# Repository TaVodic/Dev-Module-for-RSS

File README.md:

# Development Module for Safety Radar Sensor in Single-Track Vehicles

<!-- ### Features on PCB
* ESP32
    * BLE
    * MAC
    * 2 UARTs (flashing/debugging + radar interface)
    * $I^2C$ or SPI
* CP2102 USB-UART module
* PHY Ethernet module with connector
* IMU (6+3 DoF)
* Power management
* LED neopixel
* Buzzer
* Pogo pins – board to board connector
* ESP32 GPIO <-> radar pins (FFC conn)
* 100BASE-T1 connector
* ANT+ module -->

The RSS project includes two software repositories:

* ROS2 package as emulation of radar procesing unit and RSS demo module [(RSS_ROS2)](https://gitext.alps.cz/240703/rss_ros2)
* ESP-IDF project for ESP32 implementing uROS and all hardware peripherals [(RSS_uROS)](https://gitext.alps.cz/240703/rss_uros)

### [Schematic design](documents/RSS_schematic_v1.0.0.pdf)

### [Thesis](documents/Tavoda_semestral_thesis.pdf)

### [EEICT article](documents/Development_Module_for_Radar_Safety_Sensor_in_Single_Track_Vehicles.pdf)

### [Photo documentation](documents/visuals/)

### Block diagram

### Power management diagram

### ROS2 graph

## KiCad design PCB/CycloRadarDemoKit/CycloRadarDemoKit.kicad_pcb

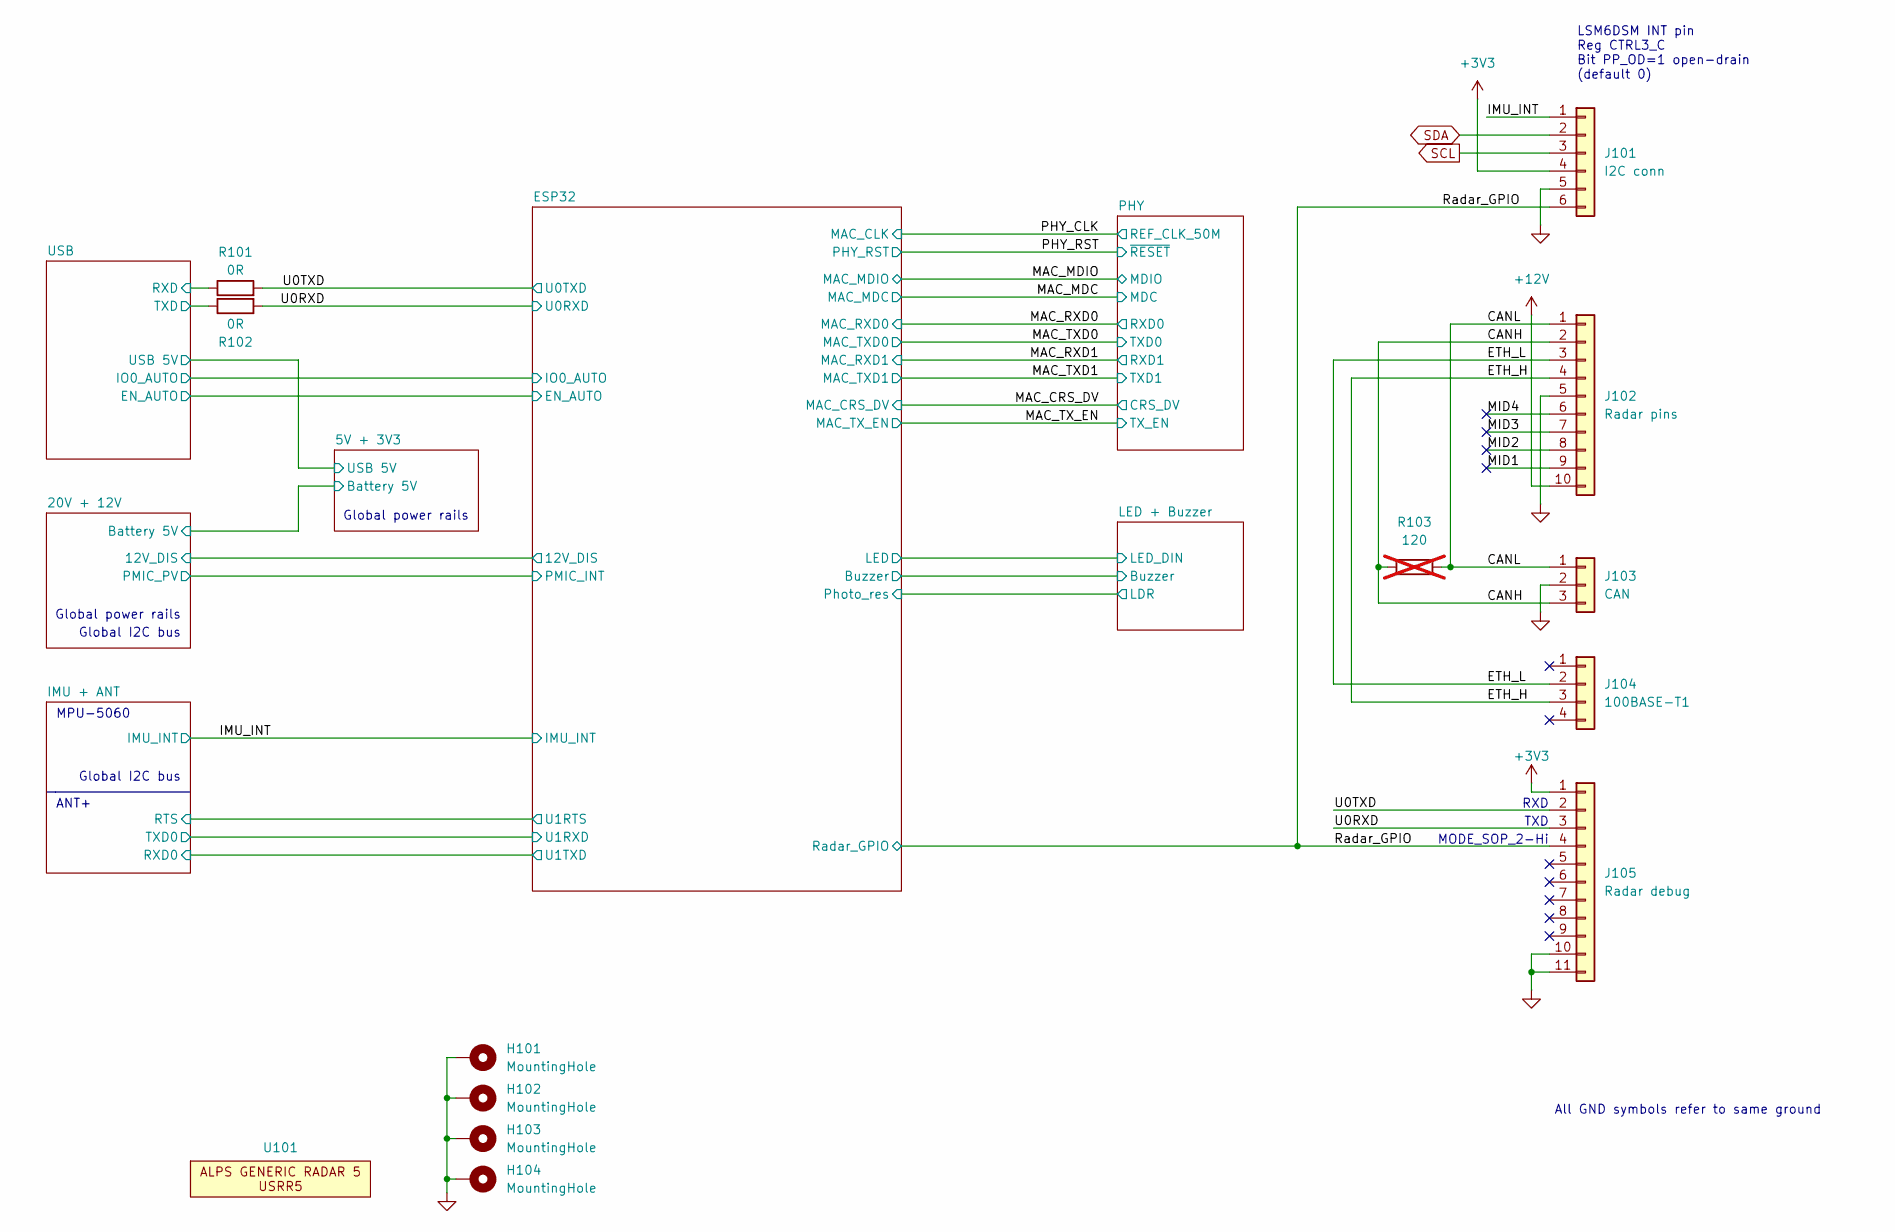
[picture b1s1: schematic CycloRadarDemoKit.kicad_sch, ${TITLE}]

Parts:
H101, H102, H103, H104: MountingHole; MountingHole_2.7mm_M2.5_ISO7380_Pad
J101: I2C conn; PinHeader_1x06_P1.27mm_Vertical
J102: Radar pins; PinHeader_1x10_P1.27mm_Vertical
J103: CAN; Molex_39501-1003; Mouser 538-39501-1003
J104: 100BASE-T1; Molex_347920040; Mouser 538-34792-0040
J105: Radar debug; AFC30-S10FCC-00; LCSC C395235
R101, R102: 0R; R_0805_2012Metric; LCSC C17477
R103: 120; R_0603_1608Metric; not fitted
U101: ALPS_USRR5_woPins

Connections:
+3V3: J101.4, J105.1; also elsewhere on the board
+12V: J102.10; also elsewhere on the board
/CANH: J102.2, J103.3, R103.1
/CANL: J102.1, J103.1, R103.2
/ETH_H: J102.4, J104.3
/ETH_L: J102.3, J104.2
/IMU_INT: J101.1; also elsewhere on the board
/MID1: J102.9
/MID2: J102.8
/MID3: J102.7
/MID4: J102.6
/Radar_GPIO: J101.6, J105.4; also elsewhere on the board
/U0RXD: J105.3, R102.2; also elsewhere on the board
/U0TXD: J105.2, R101.2; also elsewhere on the board
/USB/RXD: R101.1; also elsewhere on the board
/USB/TXD: R102.1; also elsewhere on the board
GND: H101.1, H102.1, H103.1, H104.1, J101.5, J102.5, J103.2, J105.10, J105.11; also elsewhere on the board
SCL: J101.3; also elsewhere on the board
SDA: J101.2; also elsewhere on the board

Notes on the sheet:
RXD
MPU-5060
ANT+
Global I2C bus
LSM6DSM INT pin Reg CTRL3_C Bit PP_OD=1 open-drain (default 0)
Global power rails
TXD
MODE_SOP_2-Hi
All GND symbols refer to same ground

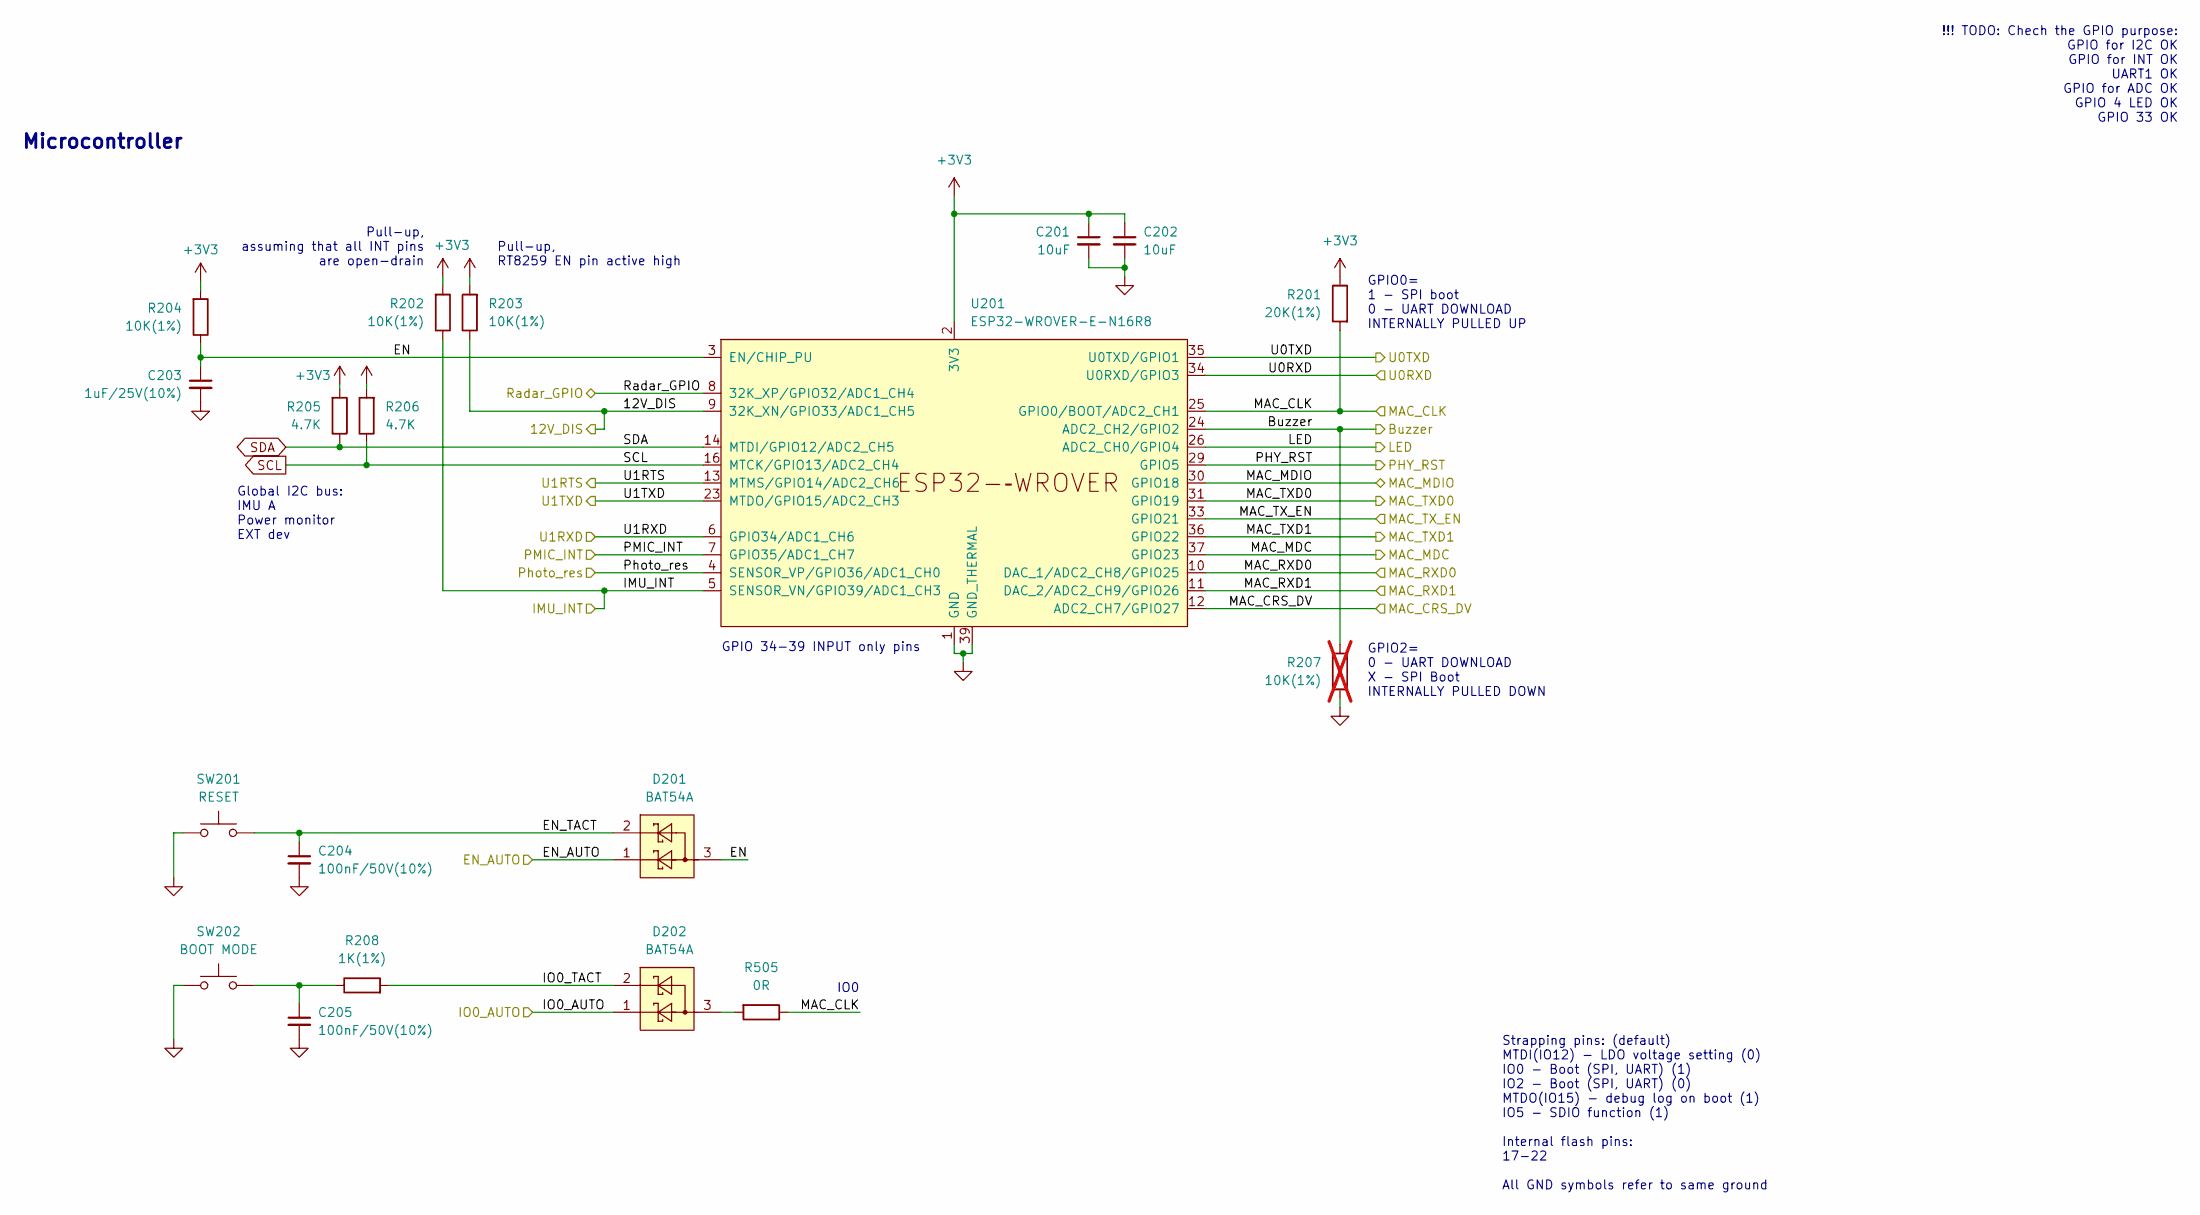
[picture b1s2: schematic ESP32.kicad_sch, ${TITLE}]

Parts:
C201, C202: 10uF; C_0603_1608Metric; LCSC C19702
C203: 1uF/25V(10%); C_0402_1005Metric; LCSC C52923
C204, C205: 100nF/50V(10%); C_0603_1608Metric; LCSC C14663
D201, D202: BAT54A; SOT-23; LCSC C283256
R201: 20K(1%); R_0603_1608Metric; LCSC C4184
R202, R203, R204: 10K(1%); R_0603_1608Metric; LCSC C25804
R205, R206: 4.7K; R_0603_1608Metric; LCSC C23162
R207: 10K(1%); R_0603_1608Metric; not fitted
R208: 1K(1%); R_0603_1608Metric; LCSC C21190
R505: 0R; R_0805_2012Metric; LCSC C17477
SW201: RESET; SW_SPST_TS-1088R; LCSC C455280
SW202: BOOT MODE; SW_SPST_TS-1088R; LCSC C455280
U201: ESP32-WROVER-E-N16R8; ESP32-WROVER-E_ThermalVias; LCSC C529589

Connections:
+3V3: C201.1, C202.1, R201.1, R202.2, R203.2, R204.2, R205.2, R206.2, U201.2 (3V3); also elsewhere on the board
/ESP32/12V_DIS: R203.1, U201.9 (32K_XN/GPIO33/ADC1_CH5); also elsewhere on the board
/ESP32/Buzzer: R207.1, U201.24 (ADC2_CH2/GPIO2); also elsewhere on the board
/ESP32/EN: C203.1, D201.3, R204.1, U201.3 (EN/CHIP_PU)
/ESP32/EN_AUTO: D201.1; also elsewhere on the board
/ESP32/EN_TACT: C204.1, D201.2, SW201.2
/ESP32/IO0_AUTO: D202.1; also elsewhere on the board
/ESP32/IO0_TACT: D202.2, R208.2
/ESP32/LED: U201.26 (ADC2_CH0/GPIO4); also elsewhere on the board
/ESP32/PMIC_INT: U201.7 (GPIO35/ADC1_CH7); also elsewhere on the board
/ESP32/Photo_res: U201.4 (SENSOR_VP/GPIO36/ADC1_CH0); also elsewhere on the board
/ESP32/U1RTS: U201.13 (MTMS/GPIO14/ADC2_CH6); also elsewhere on the board
/ESP32/U1RXD: U201.6 (GPIO34/ADC1_CH6); also elsewhere on the board
/ESP32/U1TXD: U201.23 (MTDO/GPIO15/ADC2_CH3); also elsewhere on the board
/IMU_INT: R202.1, U201.5 (SENSOR_VN/GPIO39/ADC1_CH3); also elsewhere on the board
/MAC_CRS_DV: U201.12 (ADC2_CH7/GPIO27); also elsewhere on the board
/MAC_MDC: U201.37 (GPIO23); also elsewhere on the board
/MAC_MDIO: U201.30 (GPIO18); also elsewhere on the board
/MAC_RXD0: U201.10 (DAC_1/ADC2_CH8/GPIO25); also elsewhere on the board
/MAC_RXD1: U201.11 (DAC_2/ADC2_CH9/GPIO26); also elsewhere on the board
/MAC_TXD0: U201.31 (GPIO19); also elsewhere on the board
/MAC_TXD1: U201.36 (GPIO22); also elsewhere on the board
/MAC_TX_EN: U201.33 (GPIO21); also elsewhere on the board
/PHY_CLK: R201.2, R505.1, U201.25 (GPIO0/BOOT/ADC2_CH1); also elsewhere on the board
/PHY_RST: U201.29 (GPIO5); also elsewhere on the board
/Radar_GPIO: U201.8 (32K_XP/GPIO32/ADC1_CH4); also elsewhere on the board
/U0RXD: U201.34 (U0RXD/GPIO3); also elsewhere on the board
/U0TXD: U201.35 (U0TXD/GPIO1); also elsewhere on the board
GND: C201.2, C202.2, C203.2, C204.2, C205.2, R207.2, SW201.1, SW202.1, U201.1 (GND), U201.15 (GND), U201.38 (GND), U201.39 (GND_THERMAL); also elsewhere on the board
unnamed: C205.1, R208.1, SW202.2
unnamed: D202.3, R505.2
SCL: R206.1, U201.16 (MTCK/GPIO13/ADC2_CH4); also elsewhere on the board
SDA: R205.1, U201.14 (MTDI/GPIO12/ADC2_CH5); also elsewhere on the board

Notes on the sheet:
GPIO2= 0 - UART DOWNLOAD X - SPI Boot INTERNALLY PULLED DOWN
Microcontroller
!!! TODO: Chech the GPIO purpose: GPIO for I2C OK GPIO for INT OK UART1 OK GPIO for ADC OK GPIO 4 LED OK GPIO 33 OK
Pull-up, RT8259 EN pin active high
GPIO0= 1 - SPI boot 0 - UART DOWNLOAD INTERNALLY PULLED UP
GPIO 34-39 INPUT only pins
Global I2C bus: IMU A Power monitor EXT dev
IO0
Strapping pins: (default) MTDI(IO12) - LDO voltage setting (0) IO0 - Boot (SPI, UART) (1) IO2 - Boot (SPI, UART) (0) MTDO(IO15) - debug log on boot (1) IO5 - SDIO function (1) Internal flash pins: 17-22 All GND symbols refer to same ground
Pull-up, assuming that all INT pins are open-drain

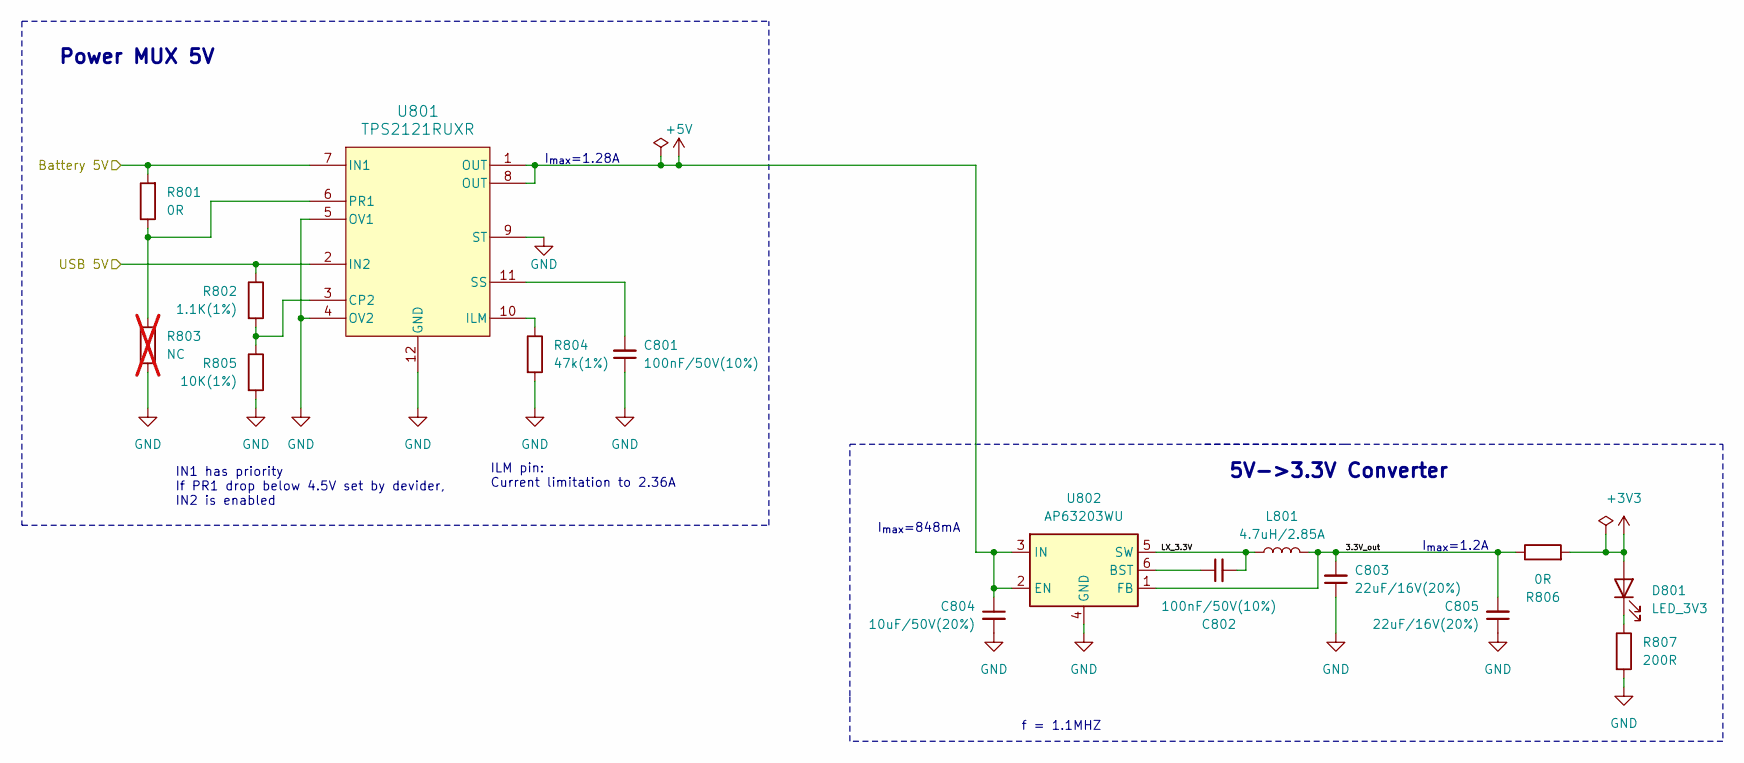
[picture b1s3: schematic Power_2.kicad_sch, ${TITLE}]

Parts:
C801, C802: 100nF/50V(10%); C_0603_1608Metric; LCSC C14663
C803, C805: 22uF/16V(20%); C_1206_3216Metric; LCSC C12891
C804: 10uF/50V(20%); C_1206_3216Metric; LCSC C13585
D801: LED_3V3; LED_0603_1608Metric; LCSC C497937
L801: 4.7uH/2.85A; L_Sunlord_SWPA4020S; LCSC C98363
R801, R806: 0R; R_0805_2012Metric; LCSC C17477
R802: 1.1K(1%); R_0603_1608Metric; LCSC C22764
R803: NC; R_0805_2012Metric; not fitted
R804: 47k(1%); R_0603_1608Metric; LCSC C25819
R805: 10K(1%); R_0603_1608Metric; LCSC C25804
R807: 200R; R_0603_1608Metric; LCSC C8218
U801: TPS2121RUXR; TPS2121; LCSC C485916
U802: AP63203WU; TSOT-23-6; LCSC C780769

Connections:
+3V3: D801.2 (A), R806.2; also elsewhere on the board
+5V: C804.1, U801.1 (OUT), U801.8 (OUT), U802.2 (EN), U802.3 (IN); also elsewhere on the board
/5V + 3V3/3.3V_out: C803.2, C805.2, L801.2, R806.1, U802.1 (FB)
/5V + 3V3/LX_3.3V: C802.2, L801.1, U802.5 (SW)
/5V + 3V3/USB 5V: R802.1, U801.2 (IN2); also elsewhere on the board
/20V + 12V/Battery 5V: R801.2, U801.7 (IN1); also elsewhere on the board
GND: C801.1, C803.1, C804.2, C805.1, R803.1, R804.2, R805.2, R807.2, U801.4 (OV2), U801.5 (OV1), U801.9 (ST), U801.12 (GND), U802.4 (GND); also elsewhere on the board
unnamed: D801.1 (K), R807.1
unnamed: R802.2, R805.1, U801.3 (CP2)
unnamed: R804.1, U801.10 (ILM)
unnamed: R801.1, R803.2, U801.6 (PR1)
unnamed: C801.2, U801.11 (SS)
unnamed: C802.1, U802.6 (BST)

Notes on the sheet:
ILM pin: Current limitation to 2.36A
IN1 has priority If PR1 drop below 4.5V set by devider, IN2 is enabled
I_{max}=1.2A
I_{max}=848mA
5V->3.3V Converter
I_{max}=1.28A
Power MUX 5V
f = 1.1MHZ

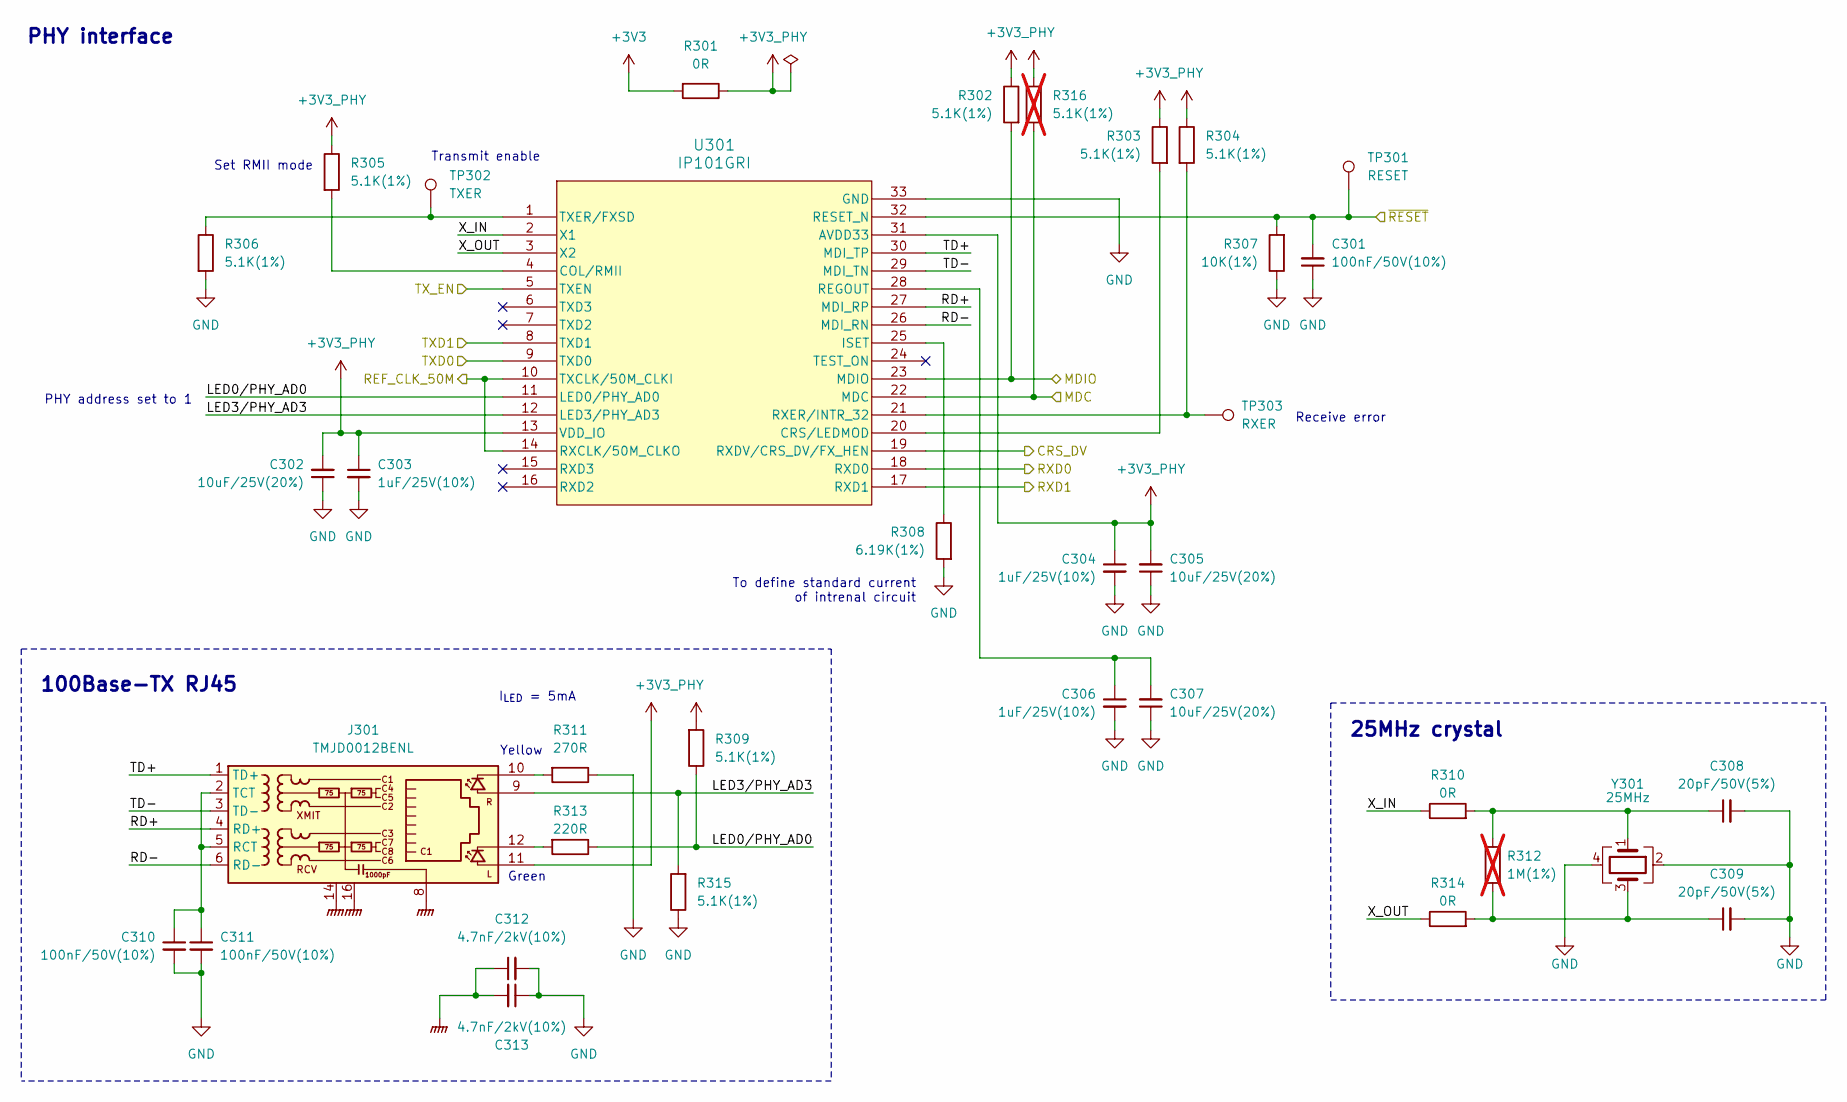
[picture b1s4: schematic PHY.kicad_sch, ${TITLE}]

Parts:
C301, C310, C311: 100nF/50V(10%); C_0603_1608Metric; LCSC C14663
C302: 10uF/25V(20%); C_0402_1005Metric; LCSC C15525
C303, C304, C306: 1uF/25V(10%); C_0402_1005Metric; LCSC C52923
C305, C307: 10uF/25V(20%); C_0603_1608Metric; LCSC C96446
C308, C309: 20pF/50V(5%); C_0402_1005Metric; LCSC C182483
C312, C313: 4.7nF/2kV(10%); C_1206_3216Metric; LCSC C41017
J301: TMJD0012BENL; RJ45_Taoglas_TMJD0012BENL; Mouser 960-TMJD0012BENL
R301: 0R; R_0805_2012Metric; LCSC C17477
R302, R303, R304, R305, R306, R309, R315: 5.1K(1%); R_0603_1608Metric; LCSC C23186
R307: 10K(1%); R_0603_1608Metric; LCSC C25804
R308: 6.19K(1%); R_0603_1608Metric; LCSC C403300
R310, R314: 0R; R_0603_1608Metric; LCSC C21189
R311: 270R; R_0603_1608Metric; LCSC C22966
R312: 1M(1%); R_0603_1608Metric; not fitted
R313: 220R; R_0603_1608Metric; LCSC C22962
R316: 5.1K(1%); R_0603_1608Metric; not fitted
TP301: RESET; TestPoint_Pad_D1.0mm
TP302: TXER; TestPoint_Pad_D1.0mm
TP303: RXER; TestPoint_Pad_D1.0mm
U301: IP101GRI; QFN_IP101GRI_WIZ; LCSC C703537
Y301: 25MHz; Crystal_SMD_3225-4Pin_3.2x2.5mm; LCSC C3003239

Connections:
+3V3: R301.2; also elsewhere on the board
+3V3_PHY: C302.2, C303.1, C304.1, C305.2, J301.11, R301.1, R302.1, R303.1, R304.1, R305.1, R309.2, R316.1, U301.13 (VDD_IO), U301.31 (AVDD33)
/MAC_CRS_DV: U301.19 (RXDV/CRS_DV/FX_HEN); also elsewhere on the board
/MAC_MDC: R316.2, U301.22 (MDC); also elsewhere on the board
/MAC_MDIO: R302.2, U301.23 (MDIO); also elsewhere on the board
/MAC_RXD0: U301.18 (RXD0); also elsewhere on the board
/MAC_RXD1: U301.17 (RXD1); also elsewhere on the board
/MAC_TXD0: U301.9 (TXD0); also elsewhere on the board
/MAC_TXD1: U301.8 (TXD1); also elsewhere on the board
/MAC_TX_EN: U301.5 (TXEN); also elsewhere on the board
/PHY/LED0/PHY_AD0: R309.1, R313.1, U301.11 (LED0/PHY_AD0)
/PHY/LED3/PHY_AD3: J301.9, R315.2, U301.12 (LED3/PHY_AD3)
/PHY/RD+: J301.4 (RD+), U301.27 (MDI_RP)
/PHY/RD-: J301.6 (RD-), U301.26 (MDI_RN)
/PHY/TD+: J301.1 (TD+), U301.30 (MDI_TP)
/PHY/TD-: J301.3 (TD-), U301.29 (MDI_TN)
/PHY/X_IN: R310.1, U301.2 (X1)
/PHY/X_OUT: R314.1, U301.3 (X2)
/PHY_CLK: U301.10 (TXCLK/50M_CLKI), U301.14 (RXCLK/50M_CLKO); also elsewhere on the board
/PHY_RST: C301.2, R307.2, TP301.1, U301.32 (RESET_N); also elsewhere on the board
GND: C301.1, C302.1, C303.2, C304.2, C305.1, C306.2, C307.1, C308.2, C309.2, C310.2, C311.2, C312.2, C313.1, R306.2, R307.1, R308.2, R311.1, R315.1, U301.33 (GND), Y301.2, Y301.4; also elsewhere on the board
GNDPWR: C312.1, C313.2, J301.8, J301.14, J301.16
unnamed: C308.1, R310.2, R312.2, Y301.1
unnamed: C309.1, R312.1, R314.2, Y301.3
unnamed: J301.10, R311.2
unnamed: J301.12, R313.2
unnamed: C310.1, C311.1, J301.2 (TCT), J301.5 (RCT)
unnamed: R305.2, U301.4 (COL/RMII)
unnamed: R303.2, U301.20 (CRS/LEDMOD)
unnamed: R308.1, U301.25 (ISET)
unnamed: C306.1, C307.2, U301.28 (REGOUT)
unnamed: R304.2, TP303.1, U301.21 (RXER/INTR_32)
unnamed: R306.1, TP302.1, U301.1 (TXER/FXSD)

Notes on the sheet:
Green
100Base-TX RJ45
I_{LED} = 5mA
25MHz crystal
PHY interface
Receive error
Set RMII mode
Yellow
Transmit enable
PHY address set to 1
To define standard current of intrenal circuit

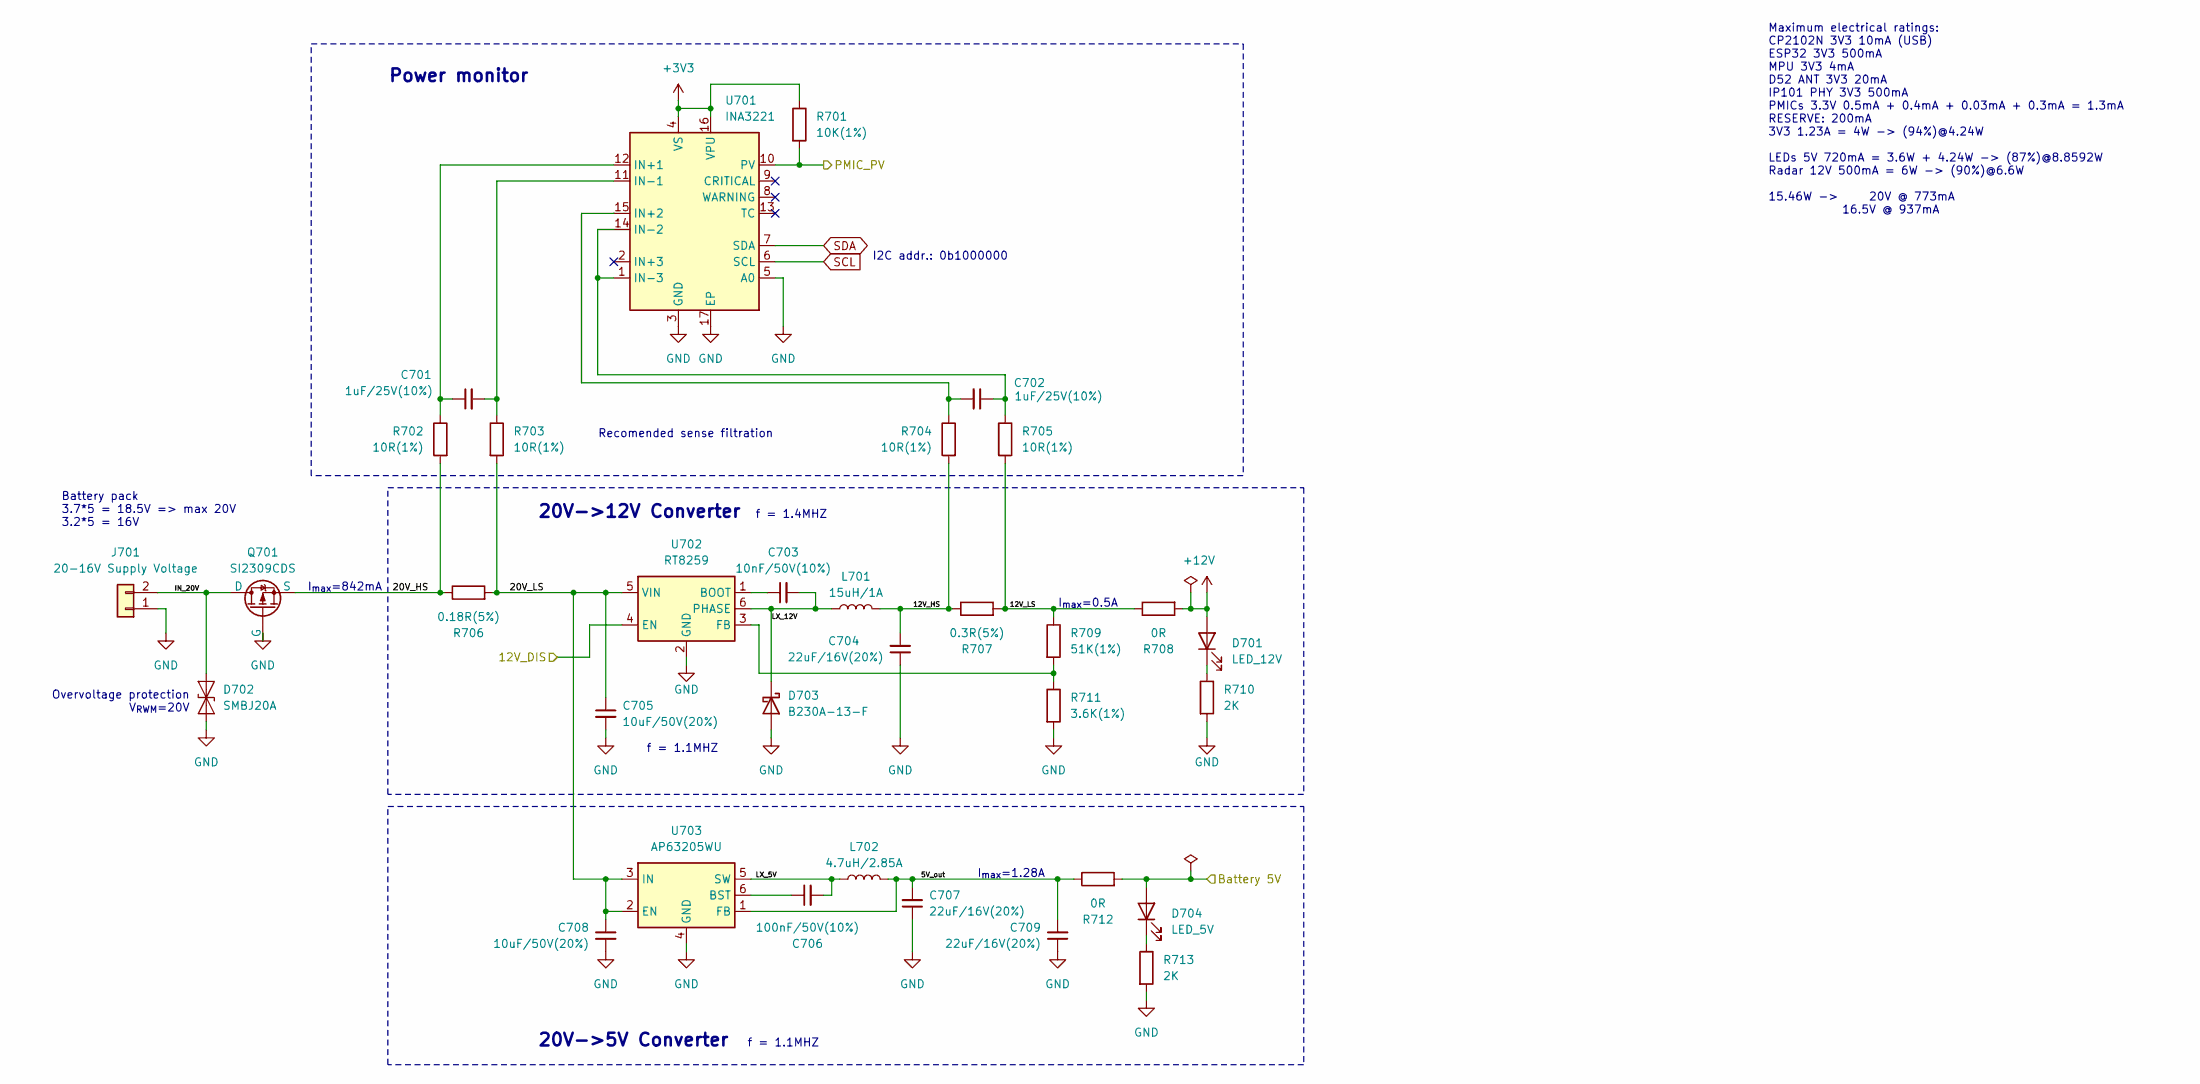
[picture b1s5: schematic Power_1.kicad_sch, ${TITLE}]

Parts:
C701, C702: 1uF/25V(10%); C_0402_1005Metric; LCSC C52923
C703: 10nF/50V(10%); C_0603_1608Metric; LCSC C57112
C704, C707, C709: 22uF/16V(20%); C_1206_3216Metric; LCSC C12891
C705, C708: 10uF/50V(20%); C_1206_3216Metric; LCSC C13585
C706: 100nF/50V(10%); C_0603_1608Metric; LCSC C14663
D701: LED_12V; LED_0603_1608Metric; LCSC C284922
D702: SMBJ20A; D_SMB; LCSC C3001979
D703: B230A-13-F; D_SMA; LCSC C12889
D704: LED_5V; LED_0603_1608Metric; LCSC C87326
J701: 20-16V Supply Voltage; Molex_39521-1002; Mouser 538-39521-1002
L701: 15uH/1A; L_Changjiang_FNR4018S; LCSC C167809
L702: 4.7uH/2.85A; L_Sunlord_SWPA4020S; LCSC C98363
Q701: SI2309CDS; SOT-23; LCSC C3021112
R701: 10K(1%); R_0603_1608Metric; LCSC C25804
R702, R703, R704, R705: 10R(1%); C_0603_1608Metric; LCSC C22859
R706: 0.18R(5%); R_Shunt_LTR10EVHJLR18; LCSC C253348
R707: 0.3R(5%); R_1210_3225Metric; LCSC C188102
R708, R712: 0R; R_0805_2012Metric; LCSC C17477
R709: 51K(1%); R_0603_1608Metric; LCSC C23196
R710, R713: 2K; R_0603_1608Metric; LCSC C22975
R711: 3.6K(1%); R_0603_1608Metric; LCSC C22980
U701: INA3221; Texas_RGV_S-PVQFN-N16_EP2.1x2.1mm; LCSC C181255
U702: RT8259; TSOT-23-6; LCSC C425775
U703: AP63205WU; TSOT-23-6; LCSC C2071056

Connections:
+3V3: R701.1, U701.4 (VS), U701.16 (VPU); also elsewhere on the board
+12V: D701.2 (A), R708.2; also elsewhere on the board
/20V + 12V/5V_out: C707.2, C709.2, L702.2, R712.1, U703.1 (FB)
/20V + 12V/12V_HS: C704.2, L701.2, R704.2, R707.1
/20V + 12V/12V_LS: R705.2, R707.2, R708.1, R709.1
/20V + 12V/20V_HS: Q701.3 (S), R702.2, R706.1
/20V + 12V/20V_LS: C705.1, C708.1, R703.2, R706.2, U702.5 (VIN), U703.2 (EN), U703.3 (IN)
/20V + 12V/Battery 5V: D704.2 (A), R712.2; also elsewhere on the board
/20V + 12V/IN_20V: D702.2 (A2), J701.2, Q701.1 (D)
/20V + 12V/LX_5V: C706.2, L702.1, U703.5 (SW)
/20V + 12V/LX_12V: C703.2, D703.1 (K), L701.1, U702.6 (PHASE)
/ESP32/12V_DIS: U702.4 (EN); also elsewhere on the board
/ESP32/PMIC_INT: R701.2, U701.10 (PV); also elsewhere on the board
GND: C704.1, C705.2, C707.1, C708.2, C709.1, D702.1 (A1), D703.2 (A), J701.1, Q701.2 (G), R710.2, R711.2, R713.2, U701.3 (GND), U701.5 (A0), U701.17 (EP), U702.2 (GND), U703.4 (GND); also elsewhere on the board
unnamed: D701.1 (K), R710.1
unnamed: D704.1 (K), R713.1
unnamed: C701.1, R702.1, U701.12 (IN+1)
unnamed: C702.2, R704.1, U701.15 (IN+2)
unnamed: C701.2, R703.1, U701.11 (IN-1)
unnamed: C702.1, R705.1, U701.1 (IN-3), U701.14 (IN-2)
unnamed: C703.1, U702.1 (BOOT)
unnamed: R709.2, R711.1, U702.3 (FB)
unnamed: C706.1, U703.6 (BST)
SCL: U701.6 (SCL); also elsewhere on the board
SDA: U701.7 (SDA); also elsewhere on the board

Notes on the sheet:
20V->5V Converter
20V->12V Converter
Overvoltage protection V_{RWM}=20V
f = 1.4MHZ
Maximum electrical ratings: CP2102N 3V3 10mA (USB) ESP32 3V3 500mA MPU 3V3 4mA D52 ANT 3V3 20mA IP101 PHY 3V3 500mA PMICs 3.3V 0.5mA + 0.4mA + 0.03mA + 0.3mA = 1.3mA RESERVE: 200mA 3V3 1.23A = 4W -> (94%)@4.24W LEDs 5V 720mA = 3.6W + 4.24W -> (87%)@8.8592W Radar 12V 500mA = 6W -> (90%)@6.6W 15.46W 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
I_{max}=842mA
I2C addr.: 0b1000000
Battery pack 3.7*5 = 18.5V => max 20V 3.2*5 = 16V
I_{max}=1.28A
Power monitor
f = 1.1MHZ
Recomended sense filtration
I_{max}=0.5A

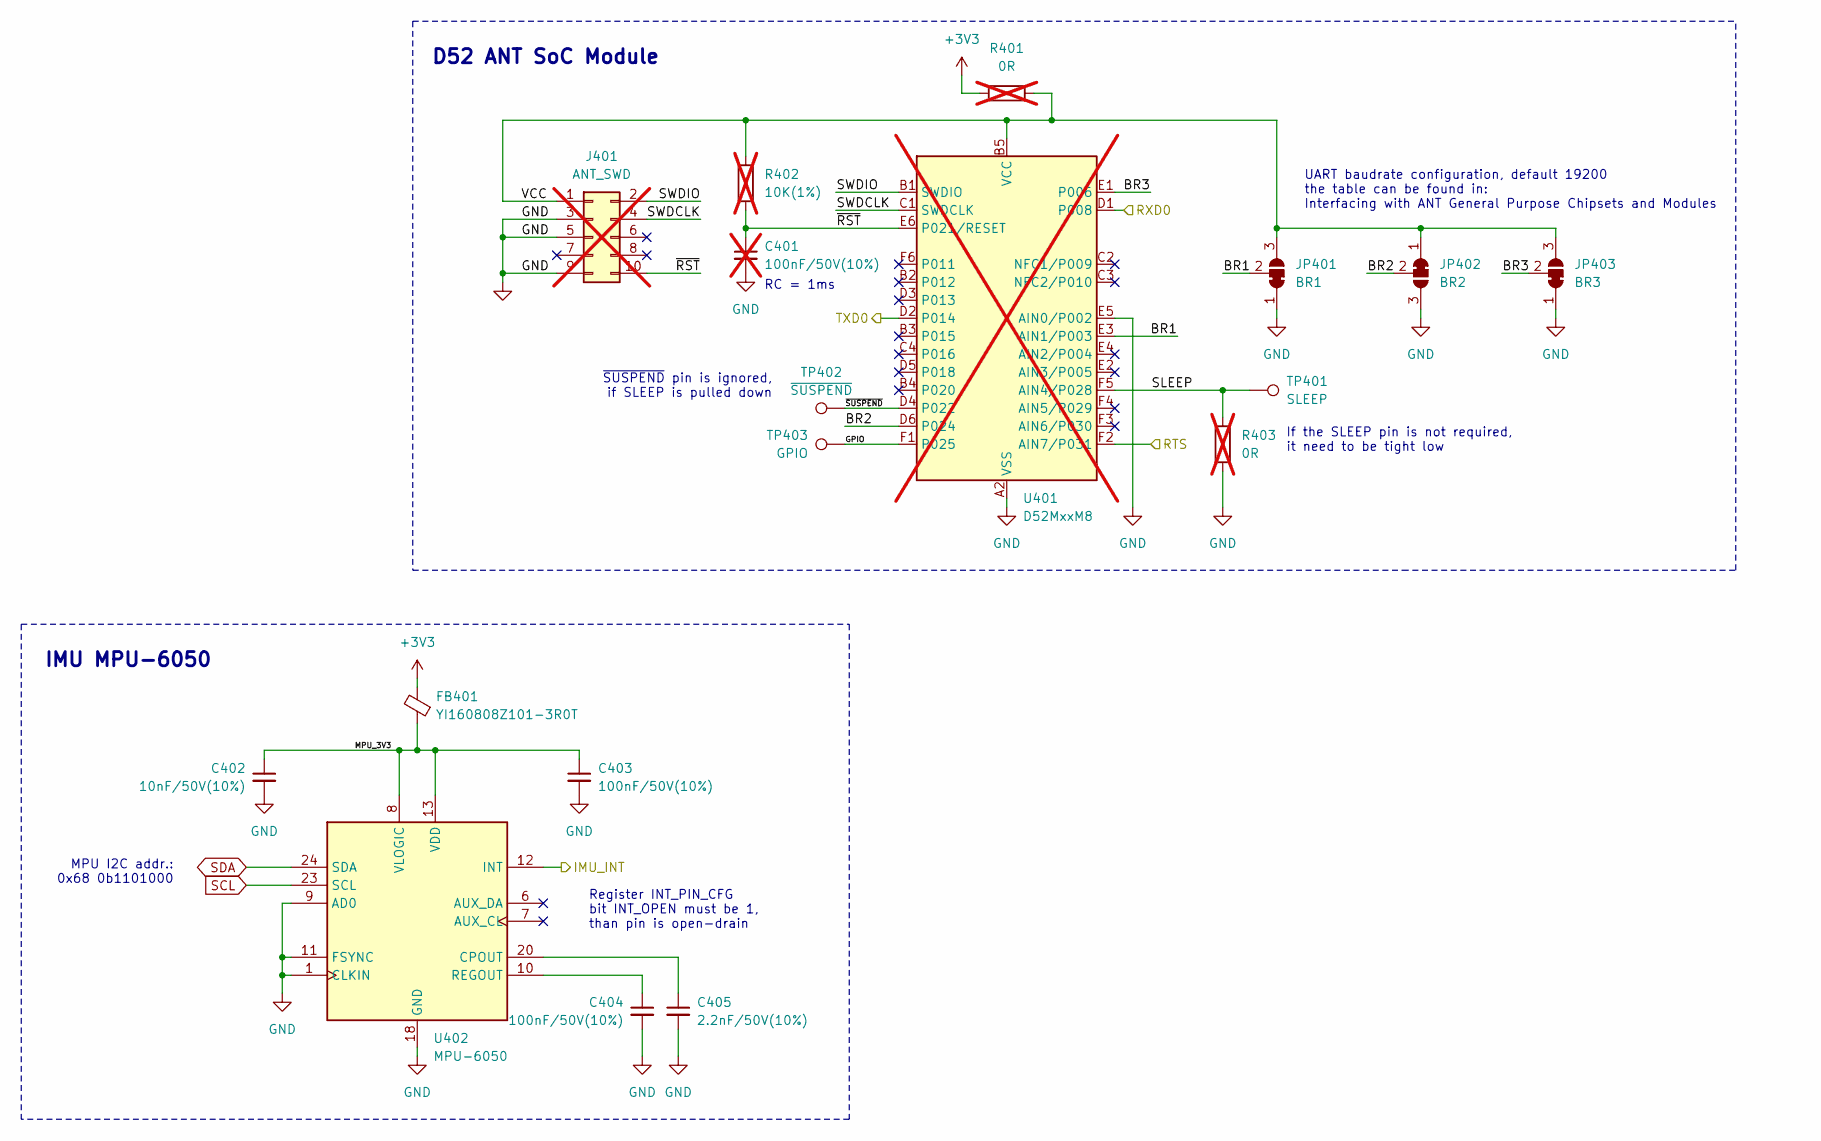
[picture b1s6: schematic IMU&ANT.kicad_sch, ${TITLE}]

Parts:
C401: 100nF/50V(10%); C_0603_1608Metric; not fitted
C402: 10nF/50V(10%); C_0402_1005Metric; LCSC C15195
C403, C404: 100nF/50V(10%); C_0603_1608Metric; LCSC C14663
C405: 2.2nF/50V(10%); C_0603_1608Metric; LCSC C1604
FB401: YI160808Z101-3R0T; R_0603_1608Metric; LCSC C3011210
J401: ANT_SWD; PinHeader_2x05_P1.27mm_Vertical_SMD; not fitted
JP401: BR1; SolderJumper-3_P1.3mm_Bridged12_RoundedPad1.0x1.5mm_NumberL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
JP402: BR2; SolderJumper-3_P1.3mm_Bridged12_RoundedPad1.0x1.5mm_NumberL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
JP403: BR3; SolderJumper-3_P1.3mm_Bridged12_RoundedPad1.0x1.5mm_NumberL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
R401, R403: 0R; R_0805_2012Metric; LCSC C17477; not fitted
R402: 10K(1%); R_0603_1608Metric; LCSC C25804; not fitted
TP401: SLEEP; TestPoint_Pad_D1.0mm
TP402: ~{SUSPEND}; TestPoint_Pad_D1.0mm
TP403: GPIO; TestPoint_Pad_D1.0mm
U401: D52MxxM8; Garmin_M8-35_9.8x14.0mm_Layout6x6_P1.5mm; DigiKey 1094-1028-ND; not fitted
U402: MPU-6050; InvenSense_QFN-24_4x4mm_P0.5mm; LCSC C24112

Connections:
+3V3: FB401.2, R401.1; also elsewhere on the board
/ESP32/U1RTS: U401.F2 (AIN7/P031); also elsewhere on the board
/ESP32/U1RXD: U401.D2 (P014); also elsewhere on the board
/ESP32/U1TXD: U401.D1 (P008); also elsewhere on the board
/IMU + ANT/BR1: JP401.2 (C), U401.E3 (AIN1/P003)
/IMU + ANT/BR2: JP402.2 (C), U401.D6 (P024)
/IMU + ANT/BR3: JP403.2 (C), U401.E1 (P006)
/IMU + ANT/GPIO: TP403.1, U401.F1 (P025)
/IMU + ANT/MPU_3V3: C402.1, C403.1, FB401.1, U402.8 (VLOGIC), U402.13 (VDD)
/IMU + ANT/SLEEP: R403.1, TP401.1, U401.F5 (AIN4/P028)
/IMU + ANT/SWDCLK: J401.4, U401.C1 (SWDCLK)
/IMU + ANT/SWDIO: J401.2, U401.B1 (SWDIO)
/IMU + ANT/VCC: J401.1, JP401.3 (B), JP402.1 (A), JP403.3 (B), R401.2, R402.2, U401.B5 (VCC), U401.B6 (VCC), U401.C5 (VCC), U401.C6 (VCC)
/IMU + ANT/~RST: C401.1, J401.10, R402.1, U401.E6 (P021/RESET)
/IMU + ANT/~SUSPEND: TP402.1, U401.D4 (P022)
/IMU_INT: U402.12 (INT); also elsewhere on the board
GND: C401.2, C402.2, C403.2, C404.2, C405.2, J401.3, J401.5, J401.9, JP401.1 (A), JP402.3 (B), JP403.1 (A), R403.2, U401.A2 (VSS), U401.A3 (VSS), U401.A4 (VSS), U401.A5 (VSS), U401.A6 (VSS), U401.E5 (AIN0/P002), U402.1 (CLKIN), U402.9 (AD0), U402.11 (FSYNC), U402.18 (GND); also elsewhere on the board
unnamed: C405.1, U402.20 (CPOUT)
unnamed: C404.1, U402.10 (REGOUT)
SCL: U402.23 (SCL); also elsewhere on the board
SDA: U402.24 (SDA); also elsewhere on the board

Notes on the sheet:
UART baudrate configuration, default 19200 the table can be found in: Interfacing with ANT General Purpose Chipsets and Modules
MPU I2C addr.: 0x68 0b1101000
D52 ANT SoC Module
~{SUSPEND} pin is ignored, if SLEEP is pulled down
Register INT_PIN_CFG bit INT_OPEN must be 1, than pin is open-drain
IMU MPU-6050
RC = 1ms
If the SLEEP pin is not required, it need to be tight low
